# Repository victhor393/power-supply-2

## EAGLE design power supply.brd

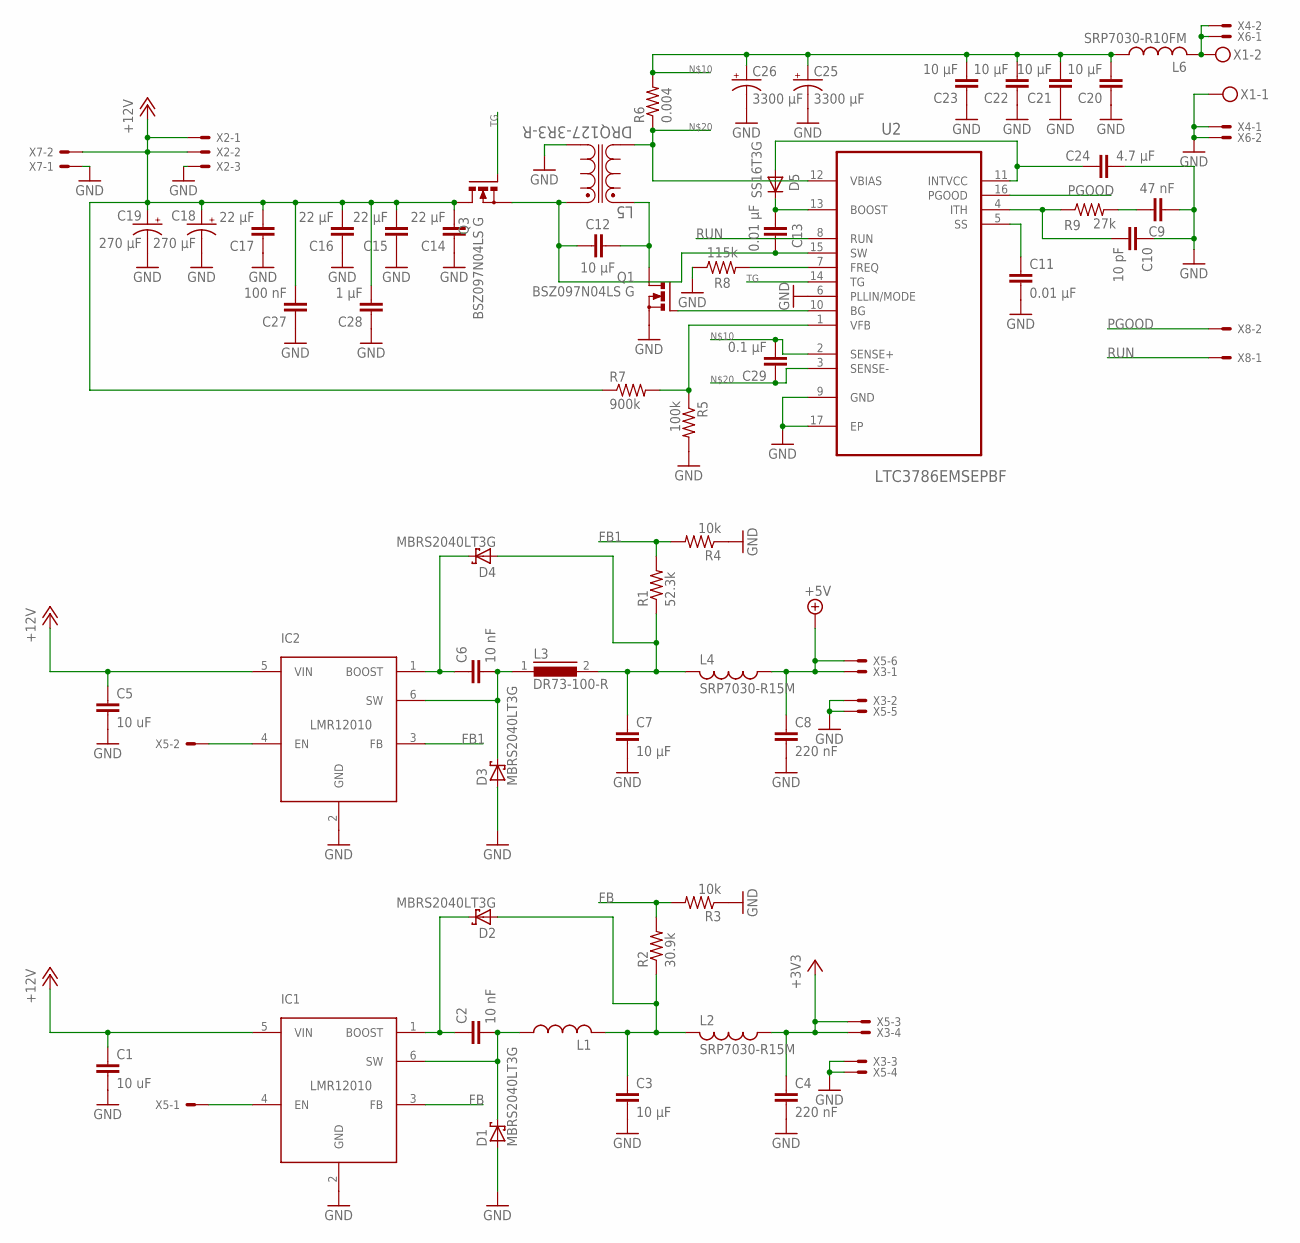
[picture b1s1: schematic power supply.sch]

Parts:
C1, C5: 10 uF; C0805
C2, C6: 10 nF; C0805
C3, C7: 10 µF; C0805
C4, C8: 220 nF; C0805
C9: 47 nF; C0805
C10: 10 pF; C0805
C11, C13: 0.01 µF; C0805
C12, C20, C21, C22, C23: 10 µF; C1210
C14, C15, C16, C17: 22 µF; C1210
C18, C19: 270 µF; E3,5-8
C24: 4.7 µF; C0805
C25, C26: 3300 µF; E7,5-16
C27: 100 nF; C0805
C28: 1 µF; C0805
C29: 0.1 µF; C0805
D1, D2, D3, D4: MBRS2040LT3G; SMB
D5: SS16T3G; DO-214AC
IC1, IC2: LMR12010; SOT23-6L
L1: SLF7045T-100M1R3-PF; SLF7045
L2, L4: SRP7030-R15M; SRP7030
L3: DR73-100-R; DR73
L5: DRQ127-3R3-R; INDM125125X800N
L6: SRP7030-R10FM; SRP7030
Q1, Q3: BSZ097N04LS G; PG-TDSON-8
R1: 52.3k; R0805
R2: 30.9k; R0805
R3, R4: 10k; R0805
R5: 100k; R0805
R6: 0.004; R2512
R7: 900k; R0805
R8: 115k; R0805
R9: 27k; R0805
U2: LTC3786EMSEPBF; SOP50P690X110-17N
X1: MKDSN1,5/2-5,08
X2: KK-156-3
X3: KK-156-4
X4: KK-156-2
X5: C-GRID-06-70543; 70543-06
X6, X7, X8: C-GRID-02-70543; 70543-02

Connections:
+3V3: C4.1, L2.1, X3.4, X5.3
+5V: C8.1, L4.1, X3.1, X5.6
+12V: C1.1, C5.1, C14.2, C15.2, C16.2, C17.2, C18.+, C19.+, C27.2, C28.2, IC1.5 (VIN), IC2.5 (VIN), Q3.5 (D), Q3.6 (D), Q3.7 (D), Q3.8 (D), Q3.TH (D), R7.1, X2.1, X2.2, X7.2
FB: IC1.3 (FB), R2.2, R3.2
FB1: IC2.3 (FB), R1.2, R4.2
GND: C1.2, C3.2, C4.2, C5.2, C7.2, C8.2, C9.2, C10.1, C11.2, C14.1, C15.1, C16.1, C17.1, C18.-, C19.-, C20.1, C21.1, C22.1, C23.1, C24.2, C25.-, C26.-, C27.1, C28.1, D1.A, D3.A, IC1.2 (GND), IC2.2 (GND), L5.4, Q1.1 (S), Q1.2 (S), Q1.3 (S), R3.1, R4.1, R5.2, R8.1, U2.6 (PLLIN/MODE), U2.9 (GND), U2.17 (EP), X1.1, X2.3, X3.2, X3.3, X4.1, X5.4, X5.5, X6.2, X7.1
unnamed: IC1.4 (EN), X5.1
unnamed: R5.1, R7.2, U2.1 (VFB)
unnamed: C2.1, D2.C, IC1.1 (BOOST)
unnamed: C2.2, D1.C, IC1.6 (SW), L1.1
unnamed: C3.1, D2.A, L1.2, L2.2, R2.1
unnamed: C6.1, D4.C, IC2.1 (BOOST)
unnamed: C6.2, D3.C, IC2.6 (SW), L3.1
unnamed: C7.1, D4.A, L3.2, L4.2, R1.1
unnamed: IC2.4 (EN), X5.2
unnamed: C20.2, C21.2, C22.2, C23.2, C25.+, C26.+, C29.2, L6.1, R6.2, U2.2 (SENSE+)
unnamed: C24.1, D5.A, U2.11 (INTVCC)
unnamed: C12.1, L5.1, Q1.5 (D), Q1.6 (D), Q1.7 (D), Q1.8 (D), Q1.TH (D)
unnamed: C10.2, R9.1, U2.4 (ITH)
unnamed: C13.1, D5.C, U2.13 (BOOST)
unnamed: C12.2, C13.2, L5.2, Q3.1 (S), Q3.2 (S), Q3.3 (S), U2.15 (SW)
unnamed: Q1.4 (G), U2.10 (BG)
unnamed: L6.2, X1.2, X4.2, X6.1
unnamed: R8.2, U2.7 (FREQ)
unnamed: C29.1, L5.3, R6.1, U2.3 (SENSE-), U2.12 (VBIAS)
unnamed: C11.1, U2.5 (SS)
unnamed: C9.1, R9.2
PGOOD: U2.16 (PGOOD), X8.2
RUN: U2.8 (RUN), X8.1
TG: Q3.4 (G), U2.14 (TG)

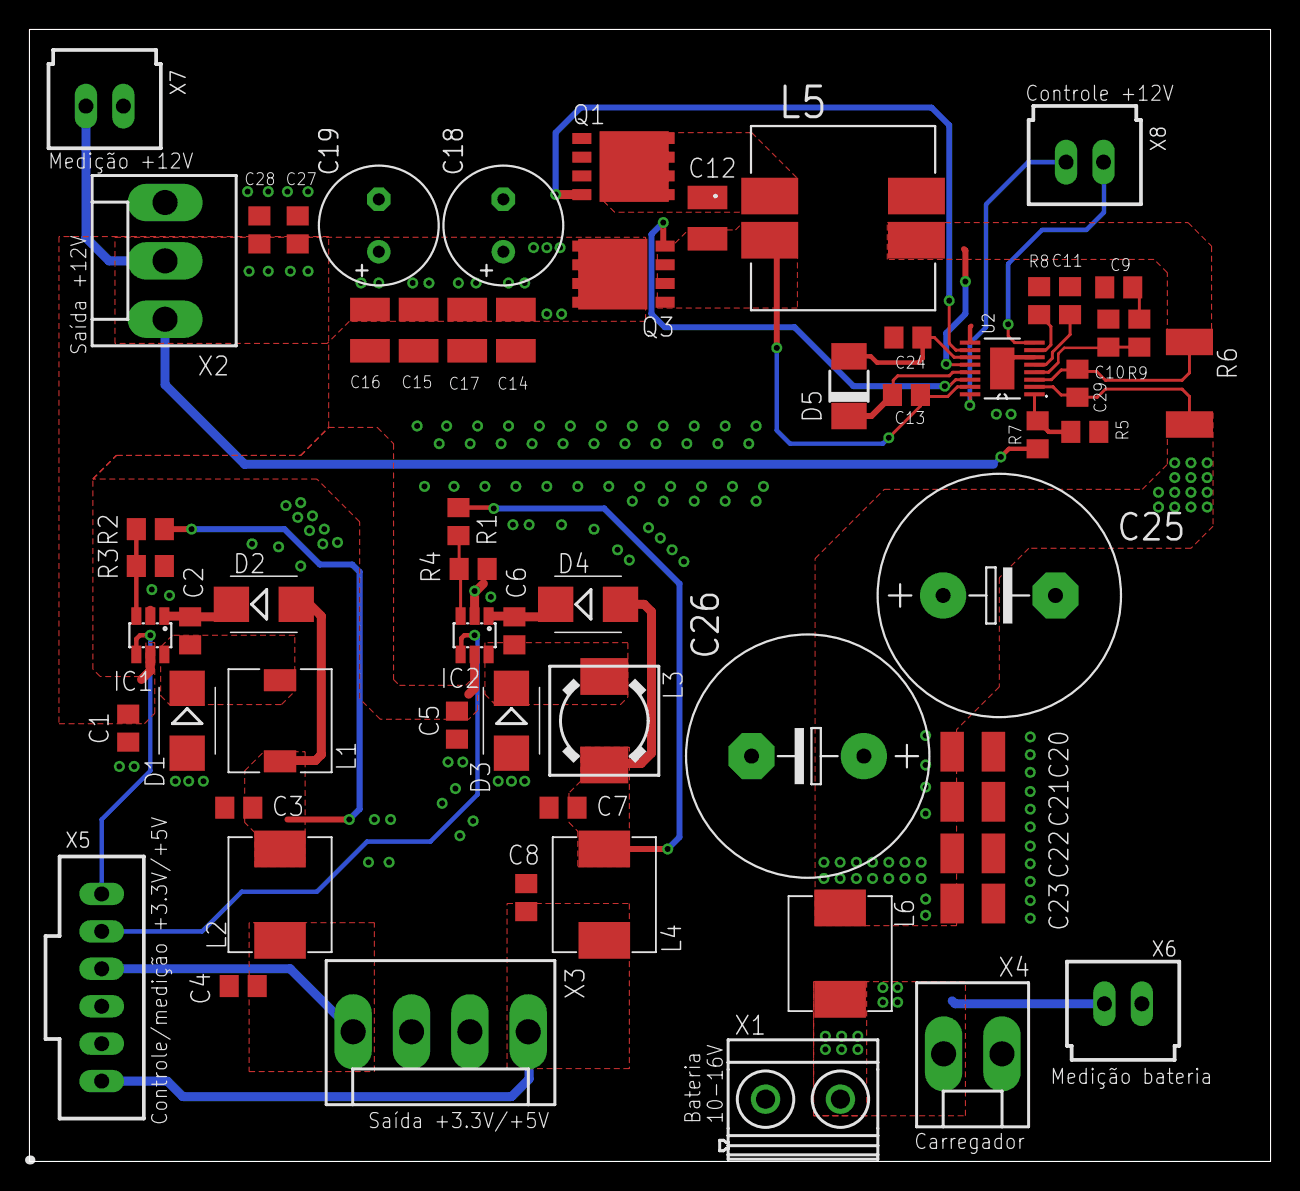
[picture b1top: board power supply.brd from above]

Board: 2 copper layers, 84.2 x 76.8 mm, 62 parts (0 on the bottom side), 30 nets.

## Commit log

2019-05-12 Initial commit fix
2019-05-21 Added schematic and board layout in pdf format
